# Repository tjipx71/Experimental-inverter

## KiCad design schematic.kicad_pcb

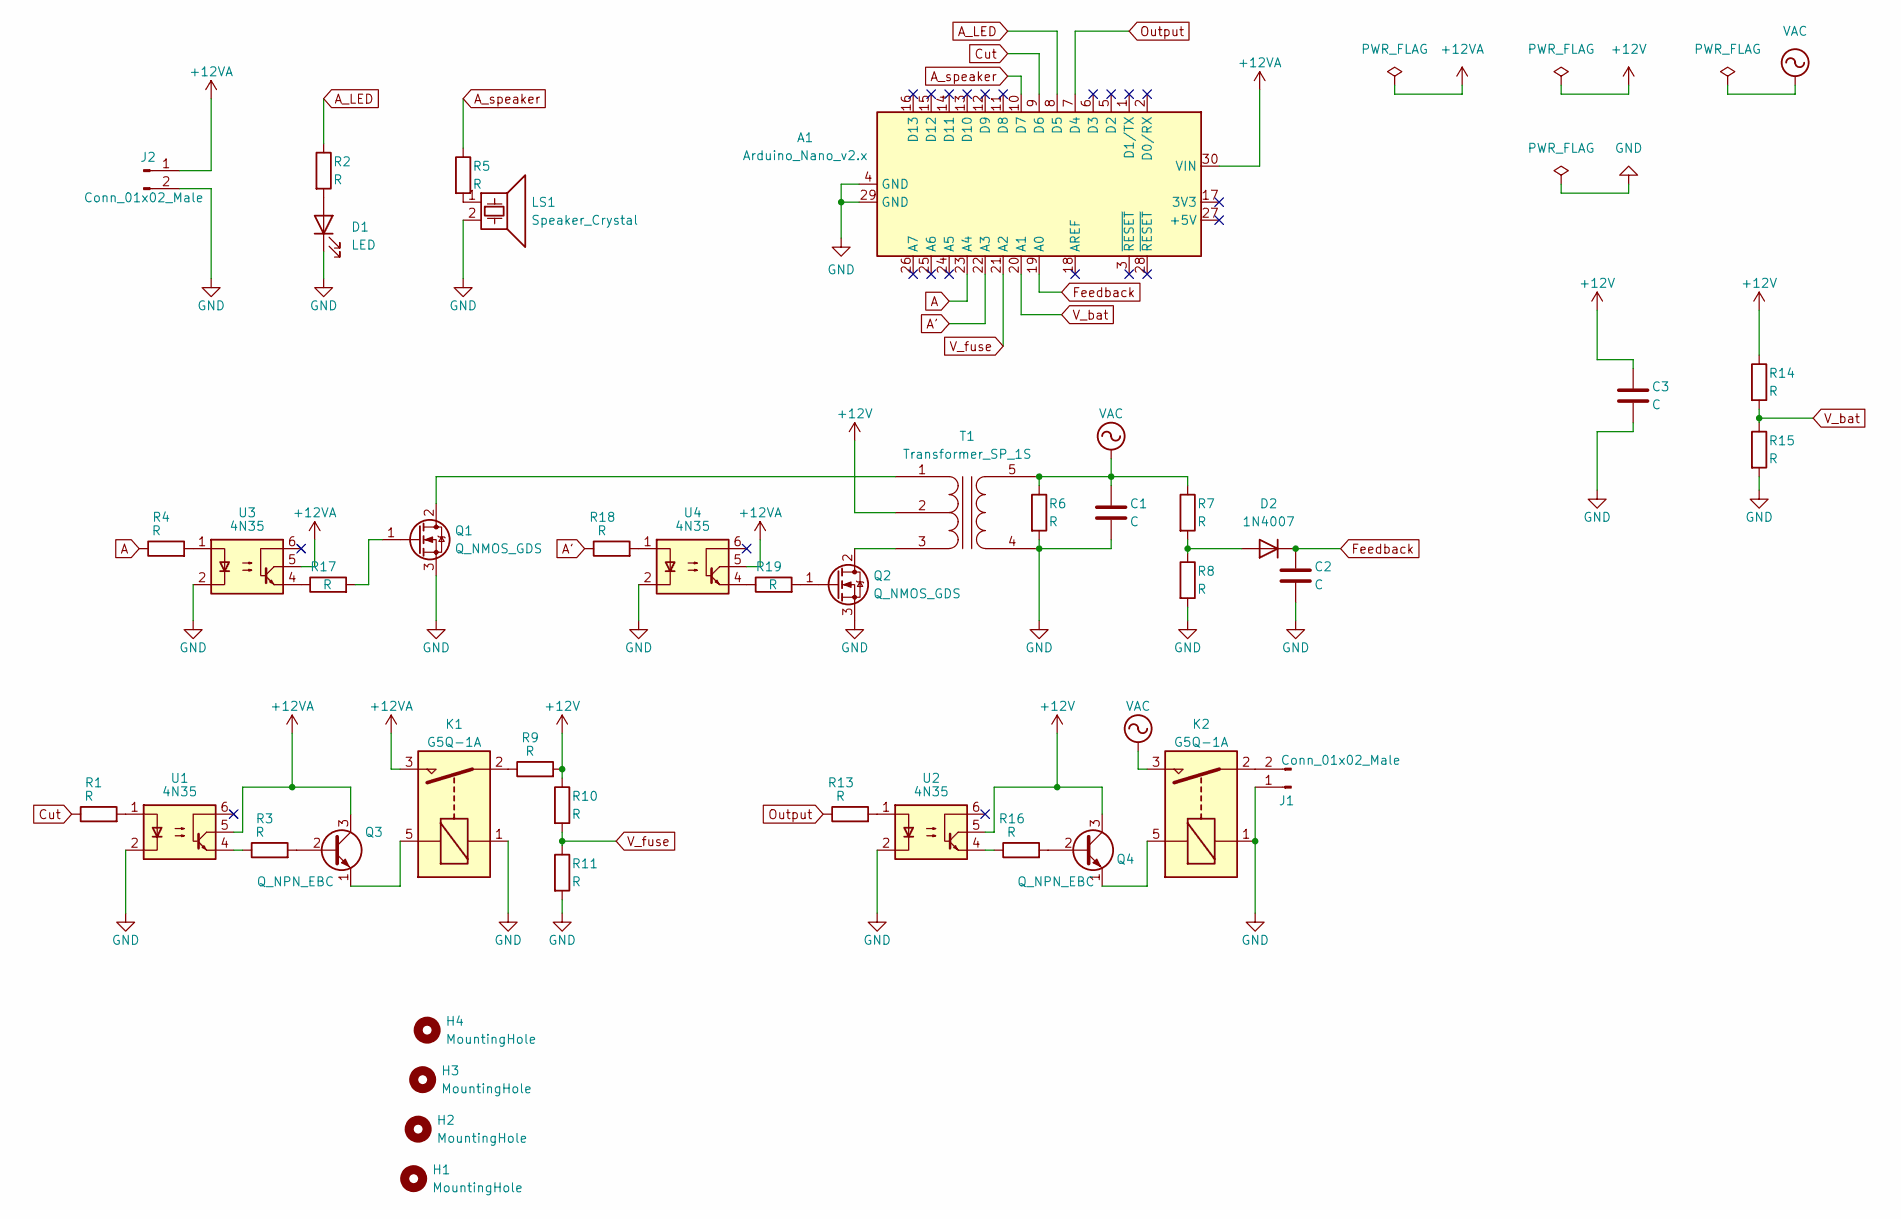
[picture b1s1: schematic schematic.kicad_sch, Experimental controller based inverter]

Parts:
A1: Arduino_Nano_v2.x; Arduino_Nano
C1, C2: C; C_Disc_D7.5mm_W5.0mm_P7.50mm
C3: C; CP_Radial_D8.0mm_P2.50mm
D1: LED; LED_D5.0mm
D2: 1N4007; D_DO-41_SOD81_P10.16mm_Horizontal
H1, H2, H3, H4: MountingHole; MountingHole_3.2mm_M3
J1, J2: Conn_01x02_Male; PinHeader_1x02_P2.54mm_Vertical
K1, K2: G5Q-1A; Relay_SPST_Omron-G5Q-1A
LS1: Speaker_Crystal; PinHeader_1x02_P2.54mm_Vertical
Q1, Q2: Q_NMOS_GDS; TO-220-3_Vertical
Q3, Q4: Q_NPN_EBC; TO-92
R1, R2, R3, R4, R5, R6, R7, R8, R9, R10, R11, R13, R14, R15, R16, R17, R18, R19: R; R_Axial_DIN0207_L6.3mm_D2.5mm_P7.62mm_Horizontal
T1: Transformer_SP_1S; Transformer_Breve_TEZ-28x33
U1, U2, U3, U4: 4N35; DIP-6_W7.62mm

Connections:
+12V: C3.1, Q4.3 (C), R9.2, R10.1, R14.1, T1.2 (PM), U2.5
+12VA: A1.30 (VIN), J2.1, K1.3, Q3.3 (C), U1.5, U3.5, U4.5; also elsewhere on the board
A: A1.23 (A4), R4.1
A': A1.22 (A3), R18.1
A_LED: A1.8 (D5), R2.1
A_speaker: A1.10 (D7), R5.1
Cut: A1.9 (D6), R1.1
Feedback: A1.19 (A0), C2.1, D2.1 (K)
GND: A1.4 (GND), A1.29 (GND), C1.2, C2.2, C3.2, D1.1 (K), J1.1, J2.2, K1.1, K2.1, LS1.2, Q1.3 (S), Q2.3 (S), R6.2, R8.2, R11.2, R15.2, T1.4 (S1), U1.2, U2.2, U3.2, U4.2; also elsewhere on the board
unnamed: D1.2 (A), R2.2
unnamed: D2.2 (A), R7.2, R8.1
unnamed 11: J1.2, K2.2; also elsewhere on the board
unnamed: K1.2, R9.1
unnamed: K1.5, Q3.1 (E)
unnamed: K2.5, Q4.1 (E)
unnamed: LS1.1, R5.2
unnamed: Q1.1 (G), R17.2
unnamed: Q1.2 (D), T1.1 (PR1)
unnamed: Q2.1 (G), R19.2
unnamed: Q2.2 (D), T1.3 (PR2)
unnamed: Q3.2 (B), R3.2
unnamed: Q4.2 (B), R16.2
unnamed: R1.2, U1.1
unnamed: R3.1, U1.4
unnamed: R4.2, U3.1
unnamed: R13.2, U2.1
unnamed: R16.1, U2.4
unnamed: R17.1, U3.4
unnamed: R18.2, U4.1
unnamed: R19.1, U4.4
Output: A1.7 (D4), R13.1
VAC: C1.1, K2.3, R6.1, R7.1, T1.5 (S2)
V_bat: A1.20 (A1), R14.2, R15.1
V_fuse: A1.21 (A2), R10.2, R11.1

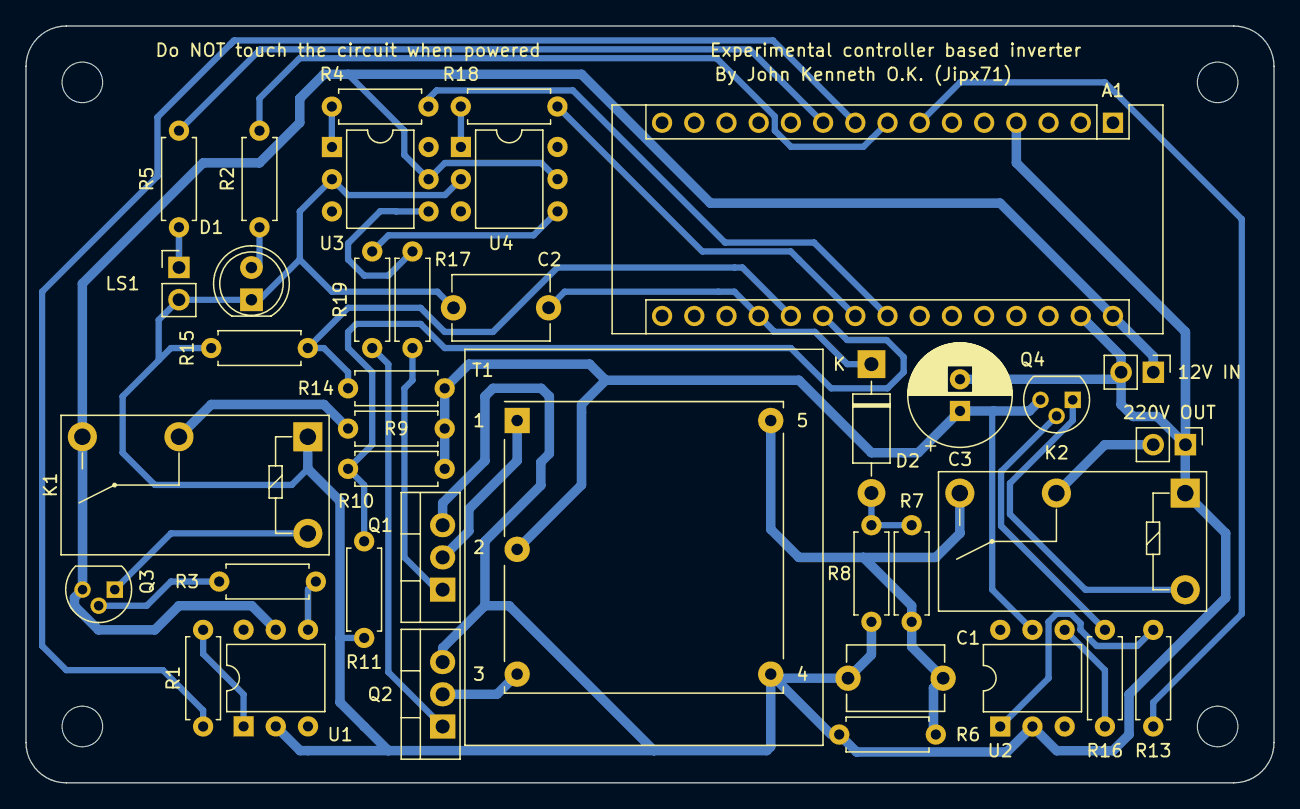
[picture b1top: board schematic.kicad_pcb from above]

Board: 2 copper layers, 98.4 x 59.7 mm, 42 parts (0 on the bottom side), 34 nets.

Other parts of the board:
12V IN, 220V OUT: Conn_01x02_Male; PinHeader_1x02_P2.54mm_Vertical

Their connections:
+12VA: 12V IN.1; also elsewhere on the board
GND: 12V IN.2, 220V OUT.1; also elsewhere on the board
unnamed 11: 220V OUT.2; also elsewhere on the board

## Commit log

2025-07-05 KICAD SCHEMATIC
